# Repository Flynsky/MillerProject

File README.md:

This design is a TOP SECRET Miller Project.

Arbeits Aufteilung:
-  Ibex-Port (Handl)
- PCB, Schematic + Layout (Gewiese)
- USB PHY, ISO7816 Interface / Card VCC-Switching, Power Domains (Belm)
- Pin Assignment, Constraints, Bringup-Testinfrastruktur - Bindeglied zwischen Hardware und HDL (Drüen)

ToDo Redesign:
- USB-Phy reindesignen (voraussichtlich TUSB1106)
- zusätzlicher USB-Connector für Device-Mode-USB und Routing zum
TUSB1106. Also Referenzimplementierung kann hier das Sonata-Board
(lowRISC) dienen
- ISO7816-Interface: Das sind nur FPGA-Pins die an PIN-Header geroutet
werden. Ggf. noch Level-Shifter
- Alles raus was wir nicht brauchen
- Bissl hübscher machen

References
- [colone chips gatemate](https://colognechip.com/programmable-logic/gatemate/)
- [reference board GateMateA1-EVB](https://github.com/OLIMEX/GateMateA1-EVB)

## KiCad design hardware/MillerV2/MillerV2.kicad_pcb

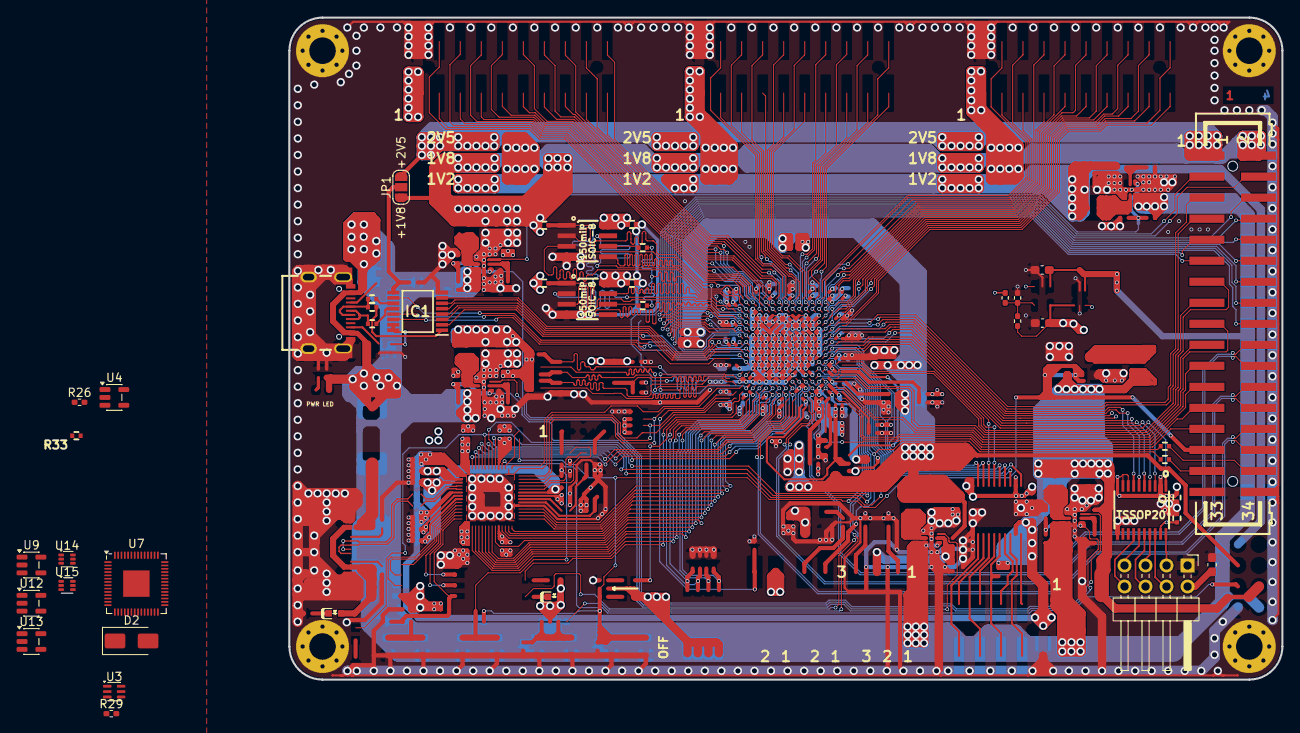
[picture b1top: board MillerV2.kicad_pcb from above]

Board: 4 copper layers, 120.0 x 80.0 mm, 45 parts (0 on the bottom side), 27 nets.

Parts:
BANK_MISC1: P-B-V-34-LF; GBH-254-SMT-34
C33, C38: 1u; C_0603_1608Metric_Pad1.08x0.95mm_HandSolder
C39, C62, C68, C69: 100n; C_0402_5MIL_DWS
C63: 22u; C_0603_1608Metric_Pad1.08x0.95mm_HandSolder
D2: SS12; D_SMA
FPGA_LED1: GREEN; LED_0603_KA
IC1: TUSB1106PWR; SOP65P640X120-16N
J1: Conn_02x04_Counter_Clockwise; PinHeader_2x04_P2.54mm_Horizontal
JP1: Jumper_3_Open; SolderJumper-3_P1.3mm_Open_RoundedPad1.0x1.5mm_NumberLabels
MH1, MH2, MH3, MH4: MountingHole_Pad; MountingHole_3.2mm_M3_Pad_Via
PWR_LED1: GREEN; LED_0603_KA
R26, R29: 10k; R_0402_1005Metric_Pad0.72x0.64mm_HandSolder
R32, R34, R35: ToDo; R_0402_1005Metric_Pad0.72x0.64mm_HandSolder
R33, R36: 1.5k; R_0402_5MIL_DWS
R37, R38: 33; R_0402_5MIL_DWS
R48, R49: 10k; R_0402_5MIL_DWS
R50, R59: 100R; R_0402_5MIL_DWS
R62, R63: 22; R_0402_5MIL_DWS
U3: TPS22919DCK; SOT-363_SC-70-6
U4, U9, U12, U13: MIC5219YM5; SOT-23-5
U6: TXB0108PWR; TSSOP20_Pitch-0.65mm_6.6x4.5x1.2mm
U7: RP2040; QFN-56-1EP_7x7mm_P0.4mm_EP3.2x3.2mm
U10, U11: LY68S3200SLT; SOIC-8_150mil
U14, U15: TPS62A02ADRL; SOT-563
USB-C2: USB-C-16P-F; USB2.0_TYPE-C(A40-00119-A52-12)_Paste

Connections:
+1V8: BANK_MISC1.2, C68.2, C69.2, JP1.1 (A), R48.1, R49.1, U10.8 (VCC), U11.8 (VCC)
+2V5: BANK_MISC1.1, C39.1, FPGA_LED1.2 (A), JP1.3 (B), U6.2 (Vcca), U6.8 (A7), U6.9 (A8), U6.10 (OE), U7.1 (IOVDD), U7.10 (IOVDD), U7.22 (IOVDD), U7.33 (IOVDD), U7.42 (IOVDD), U7.49 (IOVDD), U12.5 (OUT)
+3.3V: IC1.15 (VREG(3.3)), IC1.16 (VCC_(5.0))
+3V3: U7.43 (ADC_AVDD), U7.44 (VREG_VIN), U7.48 (USB_VDD)
+5V: C33.1, D2.1 (K), PWR_LED1.2 (A), U3.1 (IN), U4.1 (IN), U9.1 (IN), U12.1 (IN), U13.1 (IN), U14.3 (VIN), U14.4 (EN), U15.3 (VIN), U15.4 (EN), USB-C2.A4 (VBUS), USB-C2.A9 (VBUS), USB-C2.B4 (VBUS), USB-C2.B9 (VBUS)
/DirtyJtag/+1V1: U7.23 (DVDD), U7.45 (VREG_VOUT), U7.50 (DVDD)
/FB_I: R32.1, R34.2, R35.1, U4.4 (ADJ)
/ISO_AS0: J1.6, U6.16 (B4)
/ISO_AS1: J1.7, U6.15 (B5)
/ISO_AS2: J1.8, U6.14 (B6)
/ISO_CLK: J1.4, U6.18 (B2)
/ISO_IO: J1.5, U6.17 (B3)
/ISO_RST: J1.3, U6.20 (B1)
/PSRAM_CS#: R48.2, R49.2, U10.1 (#CS), U11.1 (#CS)
/PSRAM_SCLK: R62.2, R63.2
/VPU(3.3): IC1.1 (VPU(3.3)), R33.1, R36.1
/iso_5V: BANK_MISC1.5, R29.1, U3.3 (ON)
/iso_Vl: R26.1, U4.3 (EN)
<NO NET>: BANK_MISC1.33, BANK_MISC1.34, C33.2, C38.2, C39.2, C62.2, C63.2, C68.1, C69.1, IC1.8 (GND), J1.1, MH1.1 (1_1), MH2.1 (1_1), MH3.1 (1_1), MH4.1 (1_1), R26.2, R29.2, R35.2, U3.2 (GND), U4.2 (GND), U6.11 (GND), U7.19 (TESTEN), U7.57 (GND), U9.2 (GND), U10.4 (GND), U11.4 (GND), U12.2 (GND), U13.2 (GND), U14.1 (GND), U15.1 (GND), USB-C2.0 (SHELL), USB-C2.A1 (GND), USB-C2.A12 (GND), USB-C2.B1 (GND), USB-C2.B12 (GND)
ISO: C38.1, C62.1, C63.1, J1.2, R34.1, U3.6 (OUT), U4.5 (OUT), U6.19 (Vccb)
unnamed: IC1.12 (D+), R38.2
unnamed: IC1.11 (D-), R37.2
unnamed: IC1.9 (V_C_C_(_I_/O_)), JP1.2 (C)
unnamed: R62.1, U10.6 (SCLK)
unnamed: R63.1, U11.6 (SCLK)
unnamed: R36.2, R37.1, USB-C2.A7 (DN1), USB-C2.B7 (DN2)
unnamed: R33.2, R38.1, USB-C2.A6 (DP1), USB-C2.B6 (DP2)
